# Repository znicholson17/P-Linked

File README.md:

# Power Line Integrated Network Controlling Electronic Devices (P-LINKED)
## Senior Design Capstone Project
This is an ESP32 project that will demonstrate a powerline based ESP32 Smart Home system.

## Diagram of P-LINKED network

The diagram shown above describes how nodes and hub communicate with each other. For hub and nodes, the devices are connected to an electrical outlet using a powerline transciever. 
From there, each device communicates over powerline.  

Each device is limited to a theoretical speed of up to 200Mbps and 300 meters of range for IP access.

## Overview
Plug-and-play smart home integration to connect and control IoT devices over powerline and Matter standard.
The project consists of two parts:
1. Hardware
2. Software

## Hardware
For the hardware, we have created a PCB based on a ESP32-S3 with built in ethernet jack (RJ45). This PCB serves as hardware attached on top of the WisLink LX200V20 EVB boards. In the future, we plan on adapting the powerline module onto the PCB as well.

- Raspberry Pi 4 Model B
- ESP32-S3 
- WisLink LX200V20 EVB
- Custom ESP32-S3 Ethernet PCB

## Software
- [esp-idf](https://docs.espressif.com/projects/esp-idf/en/v5.2/esp32s3/get-started/index.html)
- [esp-matter](https://docs.espressif.com/projects/esp-matter/en/latest/esp32s3/developing.html#)
- [Ubuntu 20.04 LTS](https://ubuntu.com/download/desktop) or later.
- [HomeAssistant](https://www.home-assistant.io/)

## Project Structure
The project follows the recommended project structure for ESP32 applications:
- `hub/`: This folder serves as the guide for setup of a Matter hub.
- `nodes/`: This folder serves as the guide for setup and installation of an individual node(s)
- `Docs/`: This folder serves as documentation for the P-LINKED project.
- `ESP32_S3_ETH/`: This folder serves as the KiCad project file for the project.

## Getting Started
To get started, first go to [Docs](https://github.com/znicholson17/P-Linked/tree/main/Docs) folder and read the [INSTALL.md](https://github.com/znicholson17/P-Linked/blob/main/Docs/INSTALL.md).
From there, build your applications using [BUILD.md](https://github.com/znicholson17/P-Linked/blob/main/Docs/BUILD.md) and commission using [COMMISSION.md](https://github.com/znicholson17/P-Linked/blob/main/Docs/COMMISSION.md)  

### Authors

- [Zachary Nicholson](https://github.com/znicholson17)
- [Theodore Tang](https://github.com/leunknown)

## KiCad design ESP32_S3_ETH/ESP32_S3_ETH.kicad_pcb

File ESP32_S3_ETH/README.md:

# ESP32-S3 Ethernet PCB

The ESP32_S3_ETH KiCad project is a ESP32-S3 based PCB with built in Ethernet.  
The PCB has base features of a base ESP32-S3 Development board but with additional features.  

## Revision 1.0:

### Features
- Built-in 5V and 3.3V test points
- Grounded mounting points
- Programmable over UART and USB
- Wireless and Wired Connectivity
- 2 Programmable RGB LEDs
- Built to same form factor as WisLink LX200V20 EVB

### Hardware
  - ESP32-S3-WROOM-1-N16R8
  - QFN28 USB to UART Bridge
  - WizNet W5500 Ethernet Controller
  - 25Mhz Crystal Oscillators

### PCB
The first image shows the overall layout of the PCB with fills hidden and for each corresponding 3D View image, there is a built PCB image shown below.  

#### Layout of PCB

#### Front of PCB

#### Back of PCB

## Future Revision

### Features:
- Increased Connction speeds
- Powered Over Ethernet
- Configerable MAC Address
- Built-in Header Pins for plug-and-play device board stack

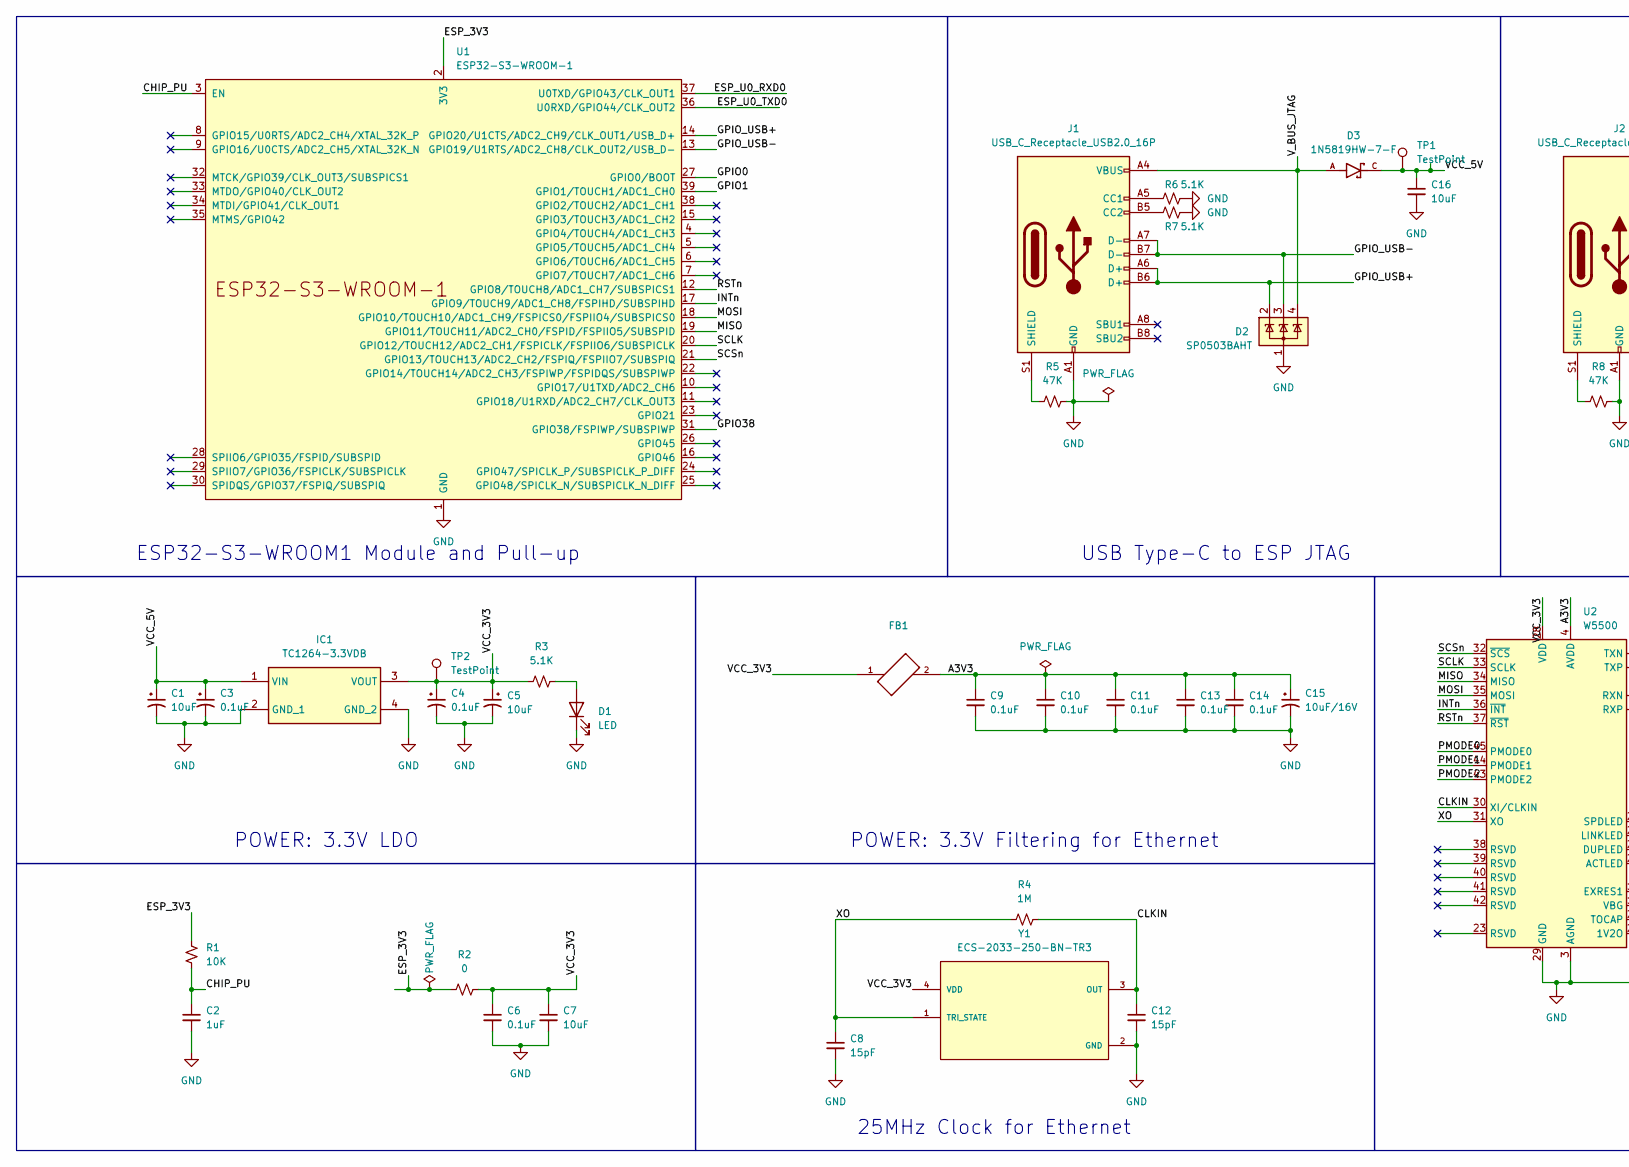
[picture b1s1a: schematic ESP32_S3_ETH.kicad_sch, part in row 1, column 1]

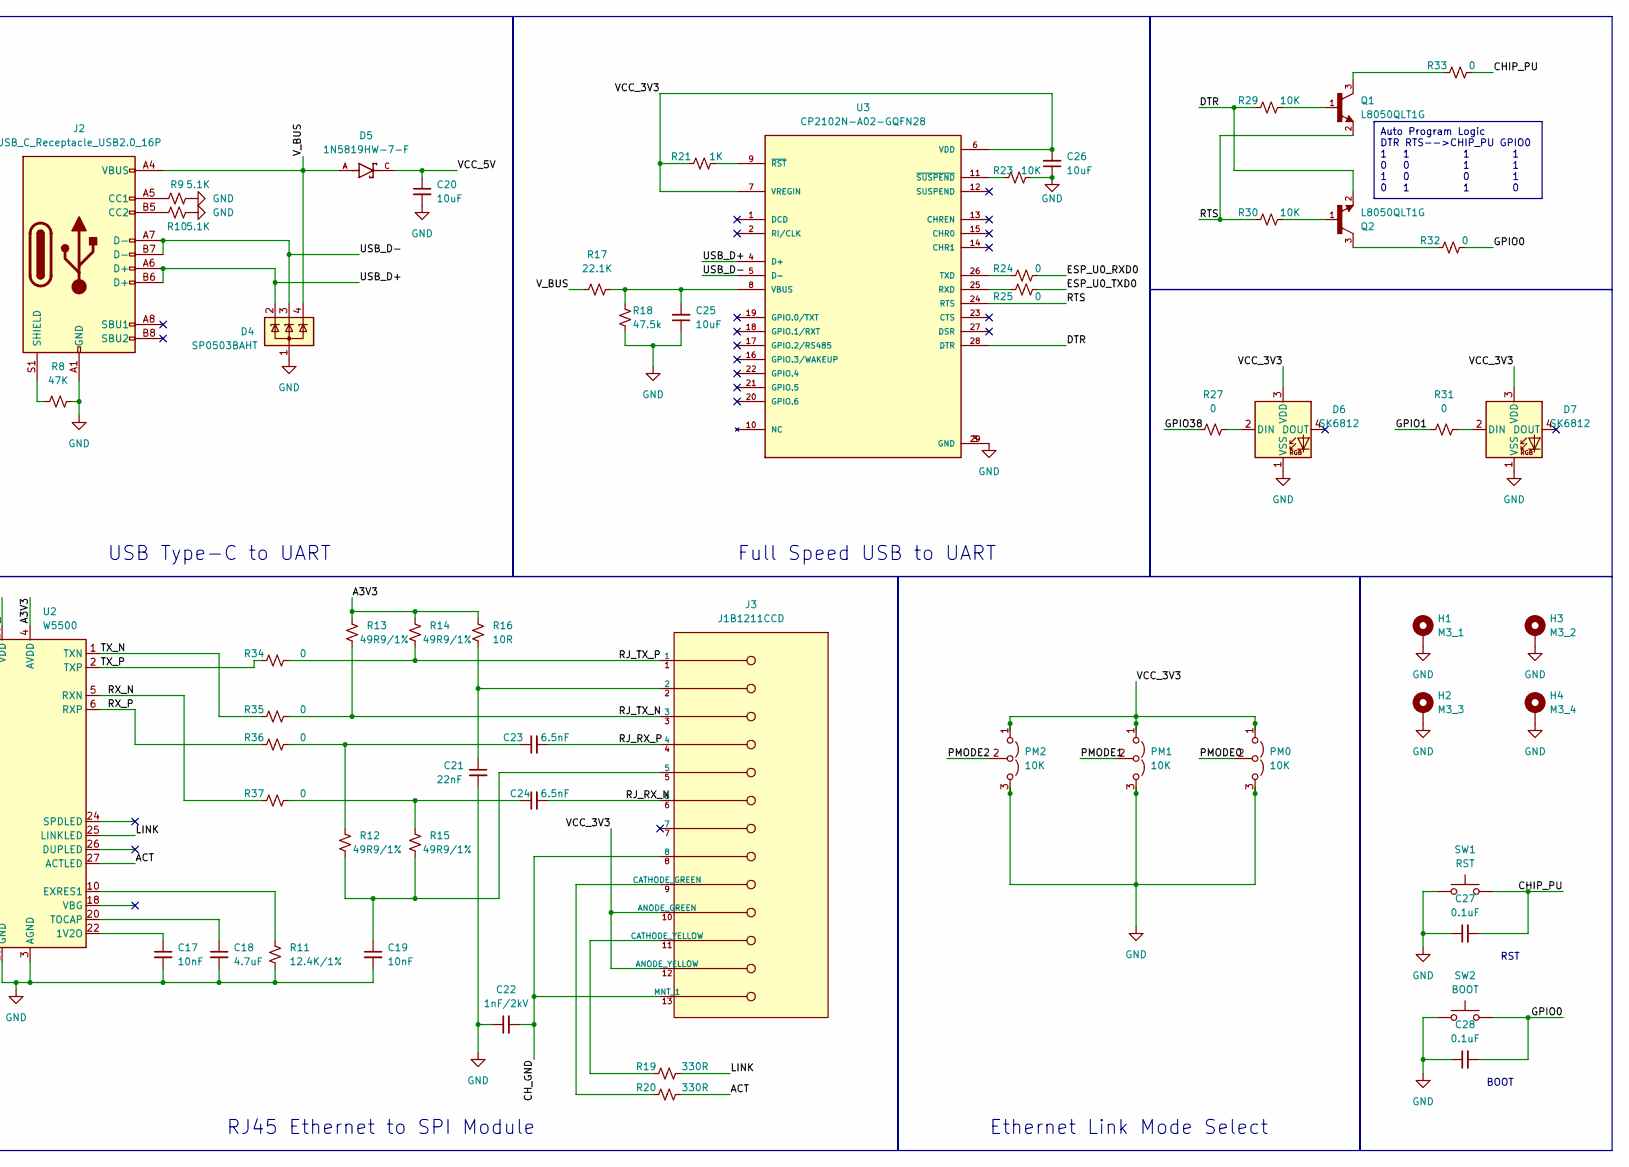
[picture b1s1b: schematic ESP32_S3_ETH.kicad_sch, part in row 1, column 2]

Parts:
C1, C5: 10uF; CP_EIA-6032-28_Kemet-C
C2: 1uF; C_0603_1608Metric
C3, C4, C6, C9, C10, C11, C13, C14, C27, C28: 0.1uF; C_0603_1608Metric
C7, C16, C20, C25, C26: 10uF; C_0603_1608Metric
C8, C12: 15pF; C_0603_1608Metric
C15: 10uF/16V; CP_EIA-6032-28_Kemet-C
C17, C19: 10nF; C_0603_1608Metric
C18: 4.7uF; C_0603_1608Metric
C21: 22nF; C_0603_1608Metric
C22: 1nF/2kV; C_1206_3216Metric
C23, C24: 6.5nF; C_0603_1608Metric
D1: LED; D_0603_1608Metric
D2, D4: SP0503BAHT; SOT-143
D3, D5: 1N5819HW-7-F; SOD3715X145N; PARTREV 18-2
D6, D7: SK6812; LED_SK6812MINI_PLCC4_3.5x3.5mm_P1.75mm
FB1: BEADC1608X95N
H1: M3_1; MountingHole_3.2mm_M3_ISO14580_Pad
H2: M3_3; MountingHole_3.2mm_M3_ISO14580_Pad
H3: M3_2; MountingHole_3.2mm_M3_ISO14580_Pad
H4: M3_4; MountingHole_3.2mm_M3_ISO14580_Pad
IC1: TC1264-3.3VDB; SOT230P700X180-4N; Manufacturer_Part_Number TC1264-3.3VDB; Mouser Part Number 579-TC1264-3.3VDB
J1, J2: USB_C_Receptacle_USB2.0_16P; USB_C_Receptacle_GCT_USB4105-xx-A_16P_TopMnt_Horizontal
J3: J1B1211CCD; RJ45_Cetus_J1B1211CCD_Horizontal; mouser part number 950-J1B1211CCD; digikey description CONN JACK 1PORT 100 BASE-T PCB
PM0, PM1, PM2: 10K; SolderJumper-3_P1.3mm_Open_Pad1.0x1.5mm
Q1, Q2: L8050QLT1G; SOT-23_MCC; PARTREV A
R1, R23, R29, R30: 10K; R_0603_1608Metric
R2, R24, R25, R27, R31, R32, R33, R34, R35, R36, R37: 0; R_0603_1608Metric
R3, R6, R7, R9, R10: 5.1K; R_0603_1608Metric
R4: 1M; R_0603_1608Metric
R5, R8: 47K; R_0603_1608Metric
R11: 12.4K/1%; R_0603_1608Metric
R12, R13, R14, R15: 49R9/1%; R_0603_1608Metric
R16: 10R; R_0603_1608Metric
R17: 22.1K; R_0603_1608Metric
R18: 47.5k; R_0603_1608Metric
R19, R20: 330R; R_0603_1608Metric
R21: 1K; R_0603_1608Metric
SW1: RST; SW_SPST_B3U-1000P
SW2: BOOT; SW_SPST_B3U-1000P
TP1, TP2: TestPoint; PinHeader_1x01_P2.54mm_Vertical
U1: ESP32-S3-WROOM-1
U2: W5500; LQFP-48_7x7mm_P0.5mm
U3: CP2102N-A02-GQFN28; QFN50P500X500X80-29N; PARTREV 1.5
Y1: ECS-2033-250-BN-TR3; OSC_ECS-2033-250-BN-TR3; PARTREV 11/15/13

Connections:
/A3V3: C9.1, C10.1, C11.1, C13.1, C14.1, C15.1, FB1.2, R13.1, R14.1, R16.1, U2.4 (AVDD), U2.8 (AVDD), U2.11 (AVDD), U2.15 (AVDD), U2.17 (AVDD), U2.21 (AVDD)
/ACT: R20.2, U2.27 (ACTLED)
/CHIP_PU: C2.1, C27.2, R1.2, R33.1, SW1.2, U1.3 (EN)
/CH_GND: C22.2, J3.8, J3.13 (MNT_1)
/CLKIN: C12.1, R4.2, U2.30 (XI/CLKIN), Y1.3 (OUT)
/DTR: Q2.2, R29.2, U3.28 (DTR)
/ESP_3V3: R1.1, R2.1, U1.2 (3V3)
/ESP_U0_RXD0: R24.2, U1.37 (U0TXD/GPIO43/CLK_OUT1)
/ESP_U0_TXD0: R25.2, U1.36 (U0RXD/GPIO44/CLK_OUT2)
/GPIO0: C28.2, R32.1, SW2.2, U1.27 (GPIO0/BOOT)
/GPIO1: R31.1, U1.39 (GPIO1/TOUCH1/ADC1_CH0)
/GPIO38: R27.1, U1.31 (GPIO38/FSPIWP/SUBSPIWP)
/GPIO_USB+: D2.2 (K), J1.A6 (D+), J1.B6 (D+), U1.14 (GPIO20/U1CTS/ADC2_CH9/CLK_OUT1/USB_D+)
/GPIO_USB-: D2.3 (K), J1.A7 (D-), J1.B7 (D-), U1.13 (GPIO19/U1RTS/ADC2_CH8/CLK_OUT2/USB_D-)
/INTn: U1.17 (GPIO9/TOUCH9/ADC1_CH8/FSPIHD/SUBSPIHD), U2.36 (~INT)
/LINK: R19.2, U2.25 (LINKLED)
/MISO: U1.19 (GPIO11/TOUCH11/ADC2_CH0/FSPID/FSPIIO5/S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), U2.34 (MISO)
/MOSI: U1.18 (GPIO10/TOUCH10/ADC1_CH9/FSPICS0/FSPIIO4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), U2.35 (MOSI)
/PMODE0: PM0.2 (C), U2.45 (PMODE0)
/PMODE1: PM1.2 (C), U2.44 (PMODE1)
/PMODE2: PM2.2 (C), U2.43 (PMODE2)
/RJ_RX_N: C24.2, J3.6
/RJ_RX_P: C23.2, J3.4
/RJ_TX_N: J3.3, R13.2, R35.2
/RJ_TX_P: J3.1, R14.2, R34.2
/RSTn: U1.12 (GPIO8/TOUCH8/ADC1_CH7/SUBSPICS1), U2.37 (~RST)
/RTS: Q1.2, R30.2, U3.24 (RTS)
/RX_N: R37.1, U2.5 (RXN)
/RX_P: R36.1, U2.6 (RXP)
/SCLK: U1.20 (GPIO12/TOUCH12/ADC2_CH1/FSPICLK/FSPIIO6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), U2.33 (SCLK)
/SCSn: U1.21 (GPIO13/TOUCH13/ADC2_CH2/FSPIQ/FSPIIO7/S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), U2.32 (~SCS)
/TX_N: R35.1, U2.1 (TXN)
/TX_P: R34.1, U2.2 (TXP)
/USB_D+: D4.2 (K), J2.A6 (D+), J2.B6 (D+), U3.4 (D+)
/USB_D-: D4.3 (K), J2.A7 (D-), J2.B7 (D-), U3.5 (D-)
/VCC_3V3: C4.1, C5.1, C6.1, C7.1, C26.2, D6.3 (VDD), D7.3 (VDD), FB1.1, IC1.3 (VOUT), J3.10 (ANODE_GREEN), J3.12 (ANODE_YELLOW), PM0.1 (A), PM1.1 (A), PM2.1 (A), R2.2, R3.1, R21.2, TP2.1, U2.28 (VDD), U3.6 (VDD), U3.7 (VREGIN), Y1.4 (VDD); also elsewhere on the board
/VCC_5V: C1.1, C3.1, C16.1, C20.1, D3.C, D5.C, IC1.1 (VIN), TP1.1; also elsewhere on the board
/V_BUS: D4.4 (K), D5.A, J2.A4 (VBUS), J2.A9 (VBUS), J2.B4 (VBUS), J2.B9 (VBUS), R17.1
/V_BUS_JTAG: D2.4 (K), D3.A, J1.A4 (VBUS), J1.A9 (VBUS), J1.B4 (VBUS), J1.B9 (VBUS)
/XO: C8.1, R4.1, U2.31 (XO), Y1.1 (TRI_STATE)
GND: C1.2, C2.2, C3.2, C4.2, C5.2, C6.2, C7.2, C8.2, C9.2, C10.2, C11.2, C12.2, C13.2, C14.2, C15.2, C16.2, C17.2, C18.2, C19.2, C20.2, C21.2, C22.1, C25.1, C26.1, C27.1, C28.1, D1.1 (K), D2.1 (A), D4.1 (A), D6.1 (VSS), D7.1 (VSS), H1.1, H2.1, H3.1, H4.1, IC1.2 (GND_1), IC1.4 (GND_2), J1.A1 (GND), J1.A12 (GND), J1.B1 (GND), J1.B12 (GND), J2.A1 (GND), J2.A12 (GND), J2.B1 (GND), J2.B12 (GND), PM0.3 (B), PM1.3 (B), PM2.3 (B), R5.1, R6.2, R7.2, R8.1, R9.2, R10.2, R11.2, R18.1, R23.1, SW1.1, SW2.1, U1.1 (GND), U1.40 (GND), U1.41 (GND), U2.3 (AGND), U2.9 (AGND), U2.14 (AGND), U2.16 (AGND), U2.19 (AGND), U2.29 (GND), U2.48 (AGND), U3.3 (GND), U3.29 (GND), Y1.2 (GND)
unnamed: C19.1, J3.5, R12.2, R15.2
unnamed: C21.1, J3.2, R16.2
unnamed: C23.1, R12.1, R36.2
unnamed: C24.1, R15.1, R37.2
unnamed: D1.2 (A), R3.2
unnamed: D6.2 (DIN), R27.2
unnamed: D7.2 (DIN), R31.2
unnamed: J1.A5 (CC1), R6.1
unnamed: J1.B5 (CC2), R7.1
unnamed: J1.S1 (SHIELD), R5.2
unnamed: J2.A5 (CC1), R9.1
unnamed: J2.B5 (CC2), R10.1
unnamed: J2.S1 (SHIELD), R8.2
unnamed: J3.9 (CATHODE_GREEN), R20.1
unnamed: J3.11 (CATHODE_YELLOW), R19.1
unnamed: Q1.1, R29.1
unnamed: Q1.3, R33.2
unnamed: Q2.1, R30.1
unnamed: Q2.3, R32.2
unnamed: C17.1, U2.22 (1V2O)
unnamed: R11.1, U2.10 (EXRES1)
unnamed: C18.1, U2.20 (TOCAP)
unnamed: R25.1, U3.25 (RXD)
unnamed: R24.1, U3.26 (TXD)
unnamed: C25.2, R17.2, R18.2, U3.8 (VBUS)
unnamed: R21.1, U3.9 (~RST)
unnamed: R23.2, U3.11 (~SUSPEND)

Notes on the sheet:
Auto Program Logic DTR RTS-->CHIP_PU GPIO0 1 1 1 1 0 0 1 1 1 0 0 1 0 1 1 0
USB Type-C to ESP JTAG
BOOT
USB Type-C to UART
RJ45 Ethernet to SPI Module
POWER: 3.3V LDO
Full Speed USB to UART
Ethernet Link Mode Select
POWER: 3.3V Filtering for Ethernet
25MHz Clock for Ethernet
RST
ESP32-S3-WROOM1 Module and Pull-up

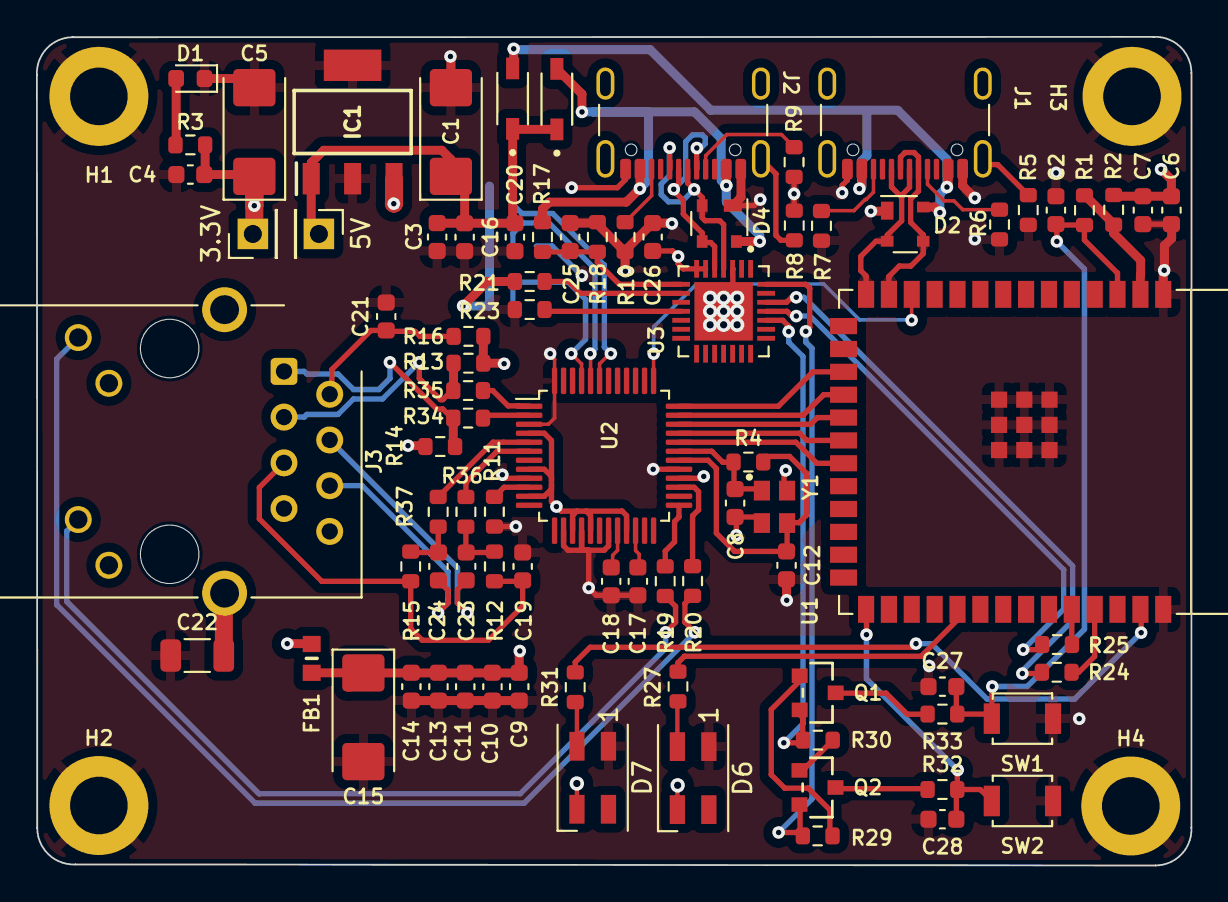
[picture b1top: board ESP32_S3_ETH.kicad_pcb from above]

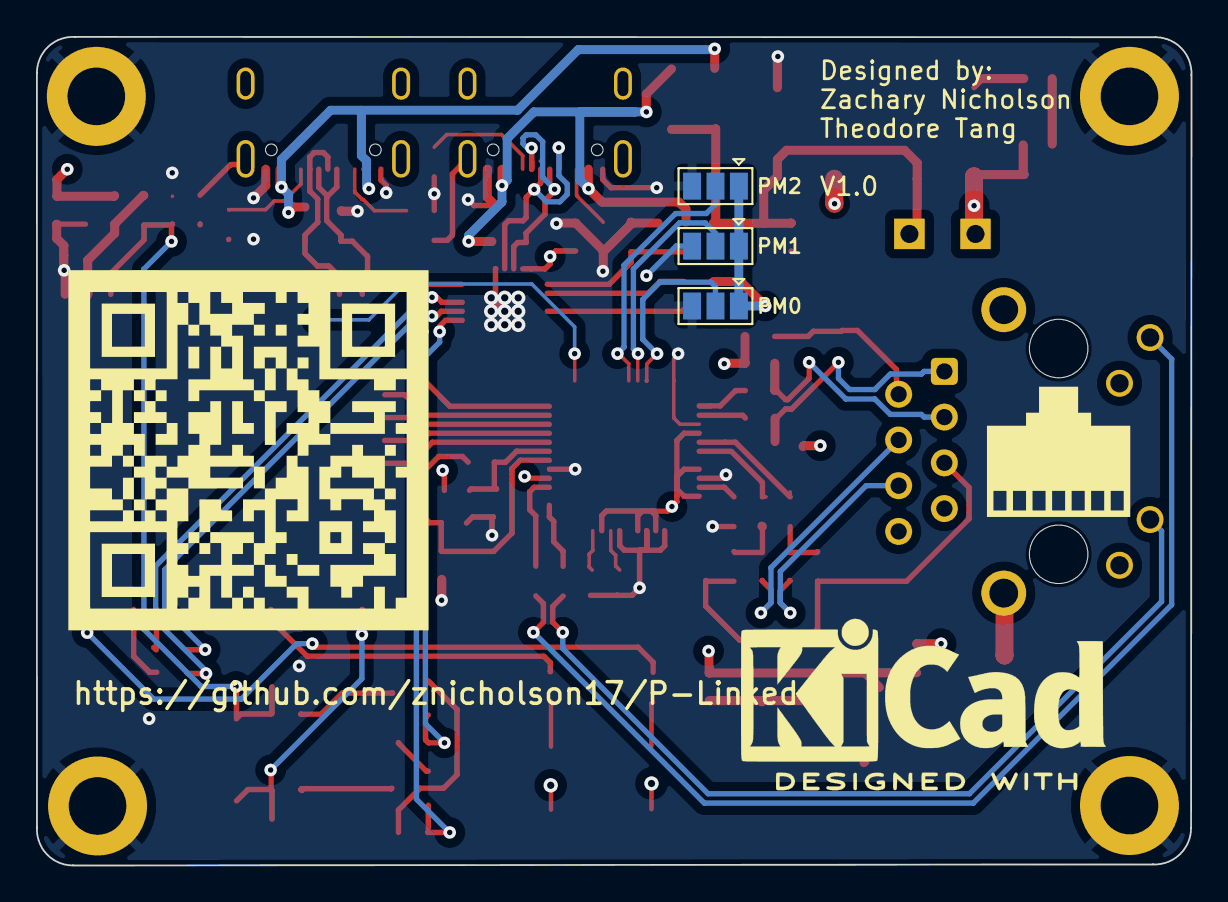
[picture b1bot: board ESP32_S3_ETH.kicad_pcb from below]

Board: 4 copper layers, 64.1 x 46.0 mm, 91 parts (3 on the bottom side), 68 nets.

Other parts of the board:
3.3V, 5V: TestPoint; PinHeader_1x01_P2.54mm_Vertical

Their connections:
/VCC_3V3: 3.3V.1; also elsewhere on the board
/VCC_5V: 5V.1; also elsewhere on the board

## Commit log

2023-10-15 Initial Progress on Hub proof-of-concept
2023-10-23 Further development on hub, socket communication, and a proof of concept thermostat node
2023-10-23 Tweaked Readme
2024-01-29 Initialized node examples and including an alpha version of the custom connectedhomeip ethernet driver
2024-02-06 Custom PCB Files
2024-02-09 Ethernet PCB Schematic completed. Light node switched to newer version of ESP-Matter
2024-02-12 ESP_ETH Schematic Finished, Routing Started on PCB
2024-02-13 Update COMMISSION.md
    fixed syntax for some code.
2024-02-14 Initial commit of the routing for the ethernet PCB for review and correction.
2024-02-16 Routing of Ethernet PCB completed, Pending further verification before finalized.
2024-02-17 Ethernet PCB finalized and ordered, hardware construction pending arrival.
2024-02-22 Create INSTALL.md
    Creating a install read.Md to help/guide users what to install.
2024-02-22 Update INSTALL.md draft
2024-02-22 Update COMMISSION.md to have highlighted bash markdowns
2024-02-23 fixed errors and update for running into errors
2024-02-23 fixed syntax mistakes
2024-02-24 Created ABSTRACT.md
2024-02-24 making more updates.
2024-02-24 more revisions, with links
2024-02-24 Create BUILD.md and write how to setup ethernet.
2024-02-25 Update ABSTRACT.md hardware portion
2024-02-25 Update BUILD.md for flashing application
2024-02-26 diagram for md file(s)
2024-02-26 added image for overview
2024-02-26 updated image and hyperlink
2024-03-15 Revised READ.md
2024-03-15 Create READ.md
    summary of other docs
2024-03-15 Added for Ethernet Driver
2024-03-15 revised images
2024-03-15 Rename READ.md to README.md
2024-03-15 Added KiCad Images
2024-03-15 Rename ESP32-S3_ETH__LAYOUT_FRONT.png to ESP32-S3_ETH_LAYOUT_FRONT.png
2024-03-15 Update README.md with images.
